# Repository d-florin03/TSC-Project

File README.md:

#  OpenBook – Dispozitiv e-book reader open-source

##  Descriere general

**OpenBook** este un e-book reader ieftin și complet open-source, dezvoltat în cadrul unui start-up care își propune să ofere o alternativă accesibilă și personalizabilă pentru cititul digital. Acest proiect este realizat în echipă, iar scopul este dezvoltarea completă a hardware-ului, de la specificații inițiale până la prototip pregătit pentru producție în masă.
## Diagrama bloc

## 📦 Componente hardware utilizate

    -> Senzor BME688 (senzor multifunctional)
    -> Buton tactil
    -> ESP32-C6-WROOM-1 (modulul principal care contine microcontrolerul ESP32-C6 si o memorie flash SPI de 8 MB)
    -> LED indicator (ADAFRUIT_CHIP-LED0603)
    -> Port USB (USB4110GFA)
    -> Conector JST de 1 mm (JST04_1MM_RA)

## ⚡ Calcul estimativ consum de energie

| Componentă             | Curent estimat | Observații                                   |
|------------------------|----------------|----------------------------------------------|
| ESP32-C6               | ~80-120 mA     | În regim activ cu WiFi                       |
| WS2812B                | ~300 mA        | La luminozitate maximă, toate LED-urile aprinse |
| Senzori proximitate    | ~10-20 mA/senzor| În funcție de tehnologia senzorului          |
| LED-uri statice        | ~10 mA/LED     | În funcție de câte sunt aprinse simultan     |

🔋 **Total estimat**: ~500–600 mA în regim activ continuu. Suficient pentru alimentare USB standard (5V, 1A).

## 📂 Fișiere utile

- `Schematic.png` – Schema electrică completă
- `PCB.png` – Randare PCB + layout
- `README.md` – Acest fișier

---

🛠️ Proiect realizat ca parte a inițiativei **OpenBook**, pentru dezvoltarea unui e-book reader ieftin și open source.

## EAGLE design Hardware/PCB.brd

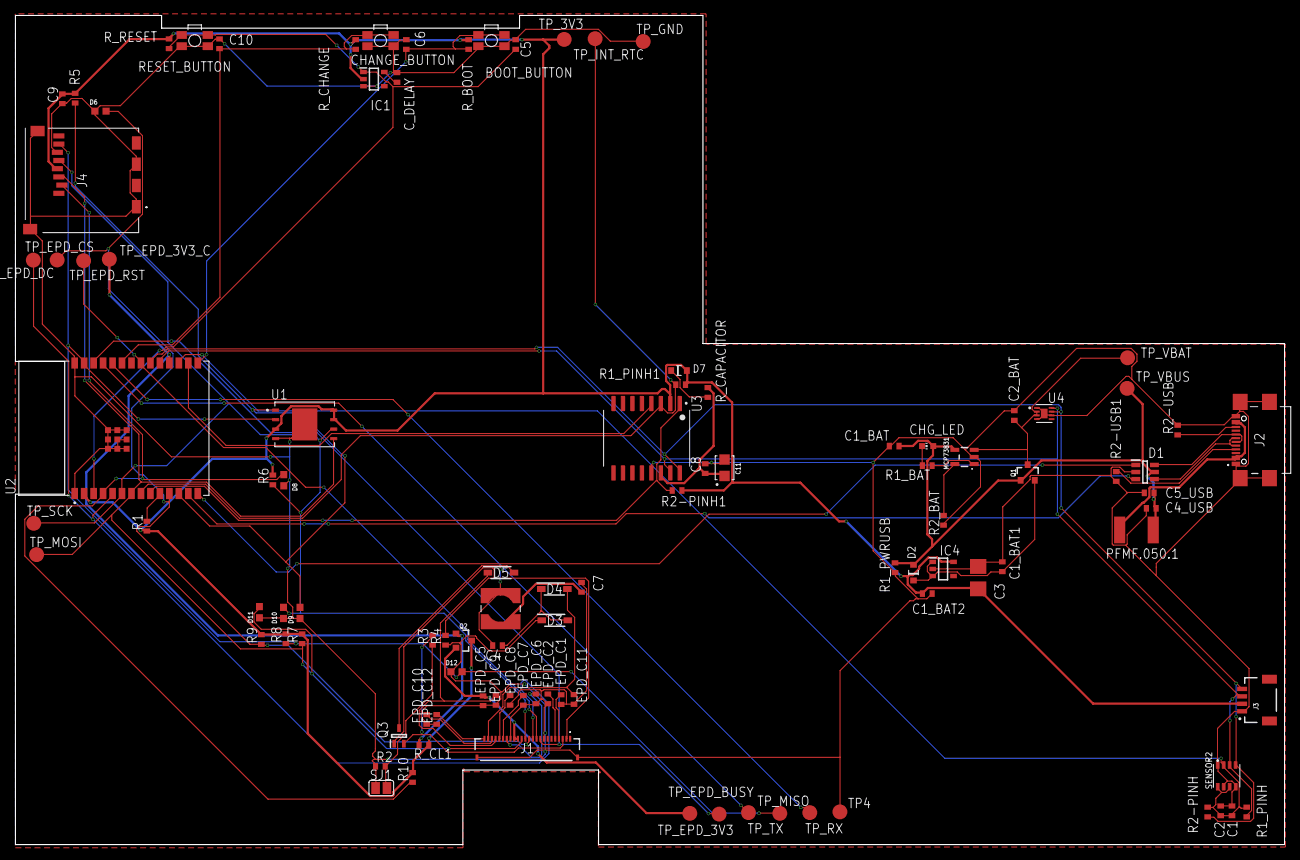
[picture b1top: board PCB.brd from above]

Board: 2 copper layers, 170.2 x 111.2 mm, 103 parts (0 on the bottom side), 56 nets.

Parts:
BOOT_BUTTON: BUTTON_CUSYOMV1; MYBUTTON
C1, C2, C4_USB, C6, C8, C9, C10: 100nF; EAGLE-LTSPICE_C0402
C1_BAT, C2_BAT, C5_USB: 4.7uF; EAGLE-LTSPICE_C0402
C1_BAT1, C1_BAT2: 4.7uF; ESP32_WROVER_EAGLE-LTSPICE_C0402
C3: 100uF TANT; RCL_CT3528
C4: 4.7uF/25V; EAGLE-LTSPICE_C0402
C5: 1uF; EAGLE-LTSPICE_C0402
C7: 10uF; EAGLE-LTSPICE_C0402
C11: CPH3225A; CAPCP3225X100N
CHANGE_BUTTON: BUTTON_CUSYOMV1; MYBUTTON
CHG_LED: ADAFRUIT_CHIP-LED0603
C_DELAY: 100nF; EAGLE-LTSPICE_C0402
D1: USBLC6-2SC6Y; SOT95P280X145-6N
D2, D7: ESP32_WROVER_AVX---SD0805S020S1R0_AVX_SD0805S020S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; ESP32_WROVER_AVX---SD0805S020S1R0_AVX_SD0805S020S1R0_0
D3, D4, D5: MBR0530; SOD3716X135N
D6, D8, D9, D10, D11, D12: PGB1010603MR; DIOC1608X36N
EPD_C1, EPD_C2, EPD_C6, EPD_C7, EPD_C8, EPD_C9, EPD_C10, EPD_C11, EPD_C12: 1uF/50V; EAGLE-LTSPICE_C0402
EPD_C5: 0.1uF/50v; EAGLE-LTSPICE_C0402
IC1: BD5229G-TR; SOT95P280X125-5N
IC4: XC6220A331MR-G; SOT95P280X120-5N
J1: FH34SRJ-24S-0.5SH_99_; FH34SRJ24S05SH99
J2: SAMACSYS_PARTS_USB4110-GF-A; SAMACSYS_PARTS_USB4110GFA
J3: QWIIC_RIGHT_ANGLE; JST04_1MM_RA
J4: 112A-TAAR-R03_ATTEND; 112ATAARR03ATTEND
L1: 68uH; IND_4828-WE-TPC_WRE
MCP73831: ESP32_WROVER_SPARKFUN-IC-POWER_MCP73831; ESP32_WROVER_SPARKFUN-IC-POWER_SOT23-5
PFMF.050.1: ESP32C6_VARISTORCN1812; ESP32C6_VARISTOR_CT/CN1812
Q1, Q2: 20V/4.2A/52mΩ/1.4W; ESP32_WROVER_SPARKFUN-DISCRETESEMI_SOT23-3
Q3: SI1308EDL-T1-GE3; SOT65P210X110-3N
R1: 10k; ESP32_WROVER_EAGLE-LTSPICE_R0402
R1_BAT: 200; ESP32_WROVER_EAGLE-LTSPICE_R0402
R1_PINH, R1_PINH1, R2-PINH, R2-PINH1, R4, R5, R6, R7, R8, R9, R10: 10K; ESP32_WROVER_EAGLE-LTSPICE_R0402
R1_PWRUSB: 100K; ESP32_WROVER_EAGLE-LTSPICE_R0402
R2: 2.2; ESP32_WROVER_EAGLE-LTSPICE_R0402
R2-USB: 5k1; ESP32_WROVER_EAGLE-LTSPICE_R0402
R2-USB1: 5K1; ESP32_WROVER_EAGLE-LTSPICE_R0402
R2_BAT: 2K; ESP32_WROVER_EAGLE-LTSPICE_R0402
R3: 0.47; ESP32_WROVER_EAGLE-LTSPICE_R0402
RESET_BUTTON: BUTTON_CUSYOMV1; MYBUTTON
R_BOOT: 10k; ESP32_WROVER_EAGLE-LTSPICE_R0402
R_CAPACITOR: 15; ESP32_WROVER_EAGLE-LTSPICE_R0402
R_CHANGE: 10k; ESP32_WROVER_EAGLE-LTSPICE_R0402
R_CL1: 10K; ESP32_WROVER_EAGLE-LTSPICE_R0402
R_RESET: 10k; ESP32_WROVER_EAGLE-LTSPICE_R0402
SENSOR2: ESP32_WROVER_BME680_BME680; ESP32_WROVER_BME680_PSON80P300X300X100-8N
SJ1: SJ
TP4: TPTP20R; TP20R
TP_3V3: TPTP20R; TP20R
TP_EPD_3V3, TP_EPD_3V3_C: TPTP20R; TP20R
TP_EPD_BUSY: TPTP20R; TP20R
TP_EPD_CS: TPTP20R; TP20R
TP_EPD_DC: TPTP20R; TP20R
TP_EPD_RST: TPTP20R; TP20R
TP_GND: TPTP20R; TP20R
TP_INT_RTC: TPTP20R; TP20R
TP_MISO: TPTP20R; TP20R
TP_MOSI: TPTP20R; TP20R
TP_RX: TPTP20R; TP20R
TP_SCK: TPTP20R; TP20R
TP_TX: TPTP20R; TP20R
TP_VBAT: TPTP20R; TP20R
TP_VBUS: TPTP20R; TP20R
U1: W25Q512JVEIQ; SON127P600X800X80-9N
U2: ESP32-C6-WROOM-1-N8; XCVR_ESP32-C6-WROOM-1-N8
U3: DS3231SN#; SOIC127P1032X265-16N
U4: MAX17048G+T10; SON50P200X200X80-9N

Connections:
3V3: C1_BAT2.1, C3.+, C9.2, D7.2, IC1.2, IC4.5, J3.2, J4.P4, Q2.3, R1.1, R1_PINH1.2, R2-PINH1.2, R5.2, R6.2, R7.2, R8.2, R9.2, R10.2, R_BOOT.2, R_CHANGE.2, R_CL1.2, R_RESET.2, TP_3V3.TP, U1.3, U1.7, U1.8, U2.2, U3.2
32KHZ: R2-PINH1.1, U2.9, U3.1
DN: D1.4, J2.A7, J2.B7
DP: D1.6, J2.A6, J2.B6
EDP_3V3: C7.1, L1.2
EPD_3V3: EPD_C5.2, J1.15, J1.16, Q2.2, TP_EPD_3V3.TP
EPD_3V3_C: Q2.1, R_CL1.1, TP_EPD_3V3_C.TP, U2.18
EPD_BUSY: J1.9, TP_EPD_BUSY.TP, U2.26
EPD_CS: D6.2, J1.12, R9.1, TP_EPD_CS.TP, U2.11
EPD_DC: J1.11, TP_EPD_DC.TP, U2.5
EPD_RST: J1.10, TP_EPD_RST.TP, U2.21
FLASH_CS: D9.2, R5.1, U1.1, U2.12
GDR: J1.2, Q3.1, R4.2
GND: BOOT_BUTTON.1, BOOT_BUTTON.2, C1.2, C1_BAT.2, C1_BAT1.2, C1_BAT2.2, C2.2, C2_BAT.2, C3.-, C4_USB.2, C5.2, C5_USB.2, C6.2, C7.2, C8.2, C9.1, C10.2, C11.2, CHANGE_BUTTON.1, CHANGE_BUTTON.2, C_DELAY.2, D1.2, D3.1, D6.1, D8.1, D9.1, D10.1, D11.1, D12.1, EPD_C1.1, EPD_C2.1, EPD_C5.1, EPD_C6.1, EPD_C7.1, EPD_C8.1, EPD_C9.1, EPD_C10.1, EPD_C11.1, EPD_C12.1, IC1.3, IC4.2, J1.8, J1.17, J1.MP1, J1.MP2, J2.A1, J2.A12, J2.B1, J2.B12, J2.MP1, J2.MP2, J2.MP3, J2.MP4, J3.1, J4.G1, J4.G2, J4.G3, J4.G4, J4.P6, MCP73831.2, R1_PWRUSB.1, R2.1, R2-USB.2, R2-USB1.1, R2_BAT.1, R4.1, RESET_BUTTON.1, RESET_BUTTON.2, SENSOR2.1, SENSOR2.5, SENSOR2.7, SJ1.1, TP4.TP, TP_GND.TP, U1.4, U1.9, U2.1, U2.28, U2.29_1, U2.29_2, U2.29_3, U2.29_4, U2.29_5, U2.29_6, U2.29_7, U2.29_8, U2.29_9, U3.13, U4.1, U4.4, U4.6, U4.9
GPIO8: R1.2, U2.10
I2C_PW: C1.1, C2.1, R1_PINH.2, R2-PINH.2, SENSOR2.2, SENSOR2.6, SENSOR2.8, U2.17
INT_RTC: R1_PINH1.1, TP_INT_RTC.TP, U2.8, U3.3
IO/BOOT: BOOT_BUTTON.3, BOOT_BUTTON.4, C6.1, R_BOOT.1, U2.15
IO/CHANGE: C10.1, CHANGE_BUTTON.3, CHANGE_BUTTON.4, R_CHANGE.1, U2.23
MISO: D12.2, J4.P7, R8.1, TP_MISO.TP, U1.2, U2.27
MOSI: D11.2, J1.14, J4.P3, R7.1, TP_MOSI.TP, U1.5, U2.7
unnamed: C4.1, D3.2, D4.1
unnamed: EPD_C12.2, J1.24
unnamed: J2.A5, R2-USB1.2
unnamed: J2.B5, R2-USB.1
unnamed: C1_BAT1.1, D2.1, IC4.1, IC4.3, Q1.2
unnamed: D7.1, R_CAPACITOR.1
unnamed: EPD_C10.2, J1.22
unnamed: EPD_C8.2, J1.20
unnamed: EPD_C7.2, J1.19
unnamed: EPD_C6.2, J1.18
unnamed: EPD_C2.2, J1.5
unnamed: C_DELAY.1, IC1.5
unnamed: EPD_C1.2, J1.4
unnamed: MCP73831.5, R2_BAT.2
unnamed: CHG_LED.C, R1_BAT.1
unnamed: MCP73831.1, R1_BAT.2
PREVGH: D5.1, EPD_C9.2, J1.21
PREVGL: D4.2, EPD_C11.2, J1.23
RESE: J1.3, Q3.2, R3.2
RESET: C5.1, IC1.1, RESET_BUTTON.3, RESET_BUTTON.4, R_RESET.1, U2.3
RESE`: R2.2, R3.1, SJ1.2
RTC_RST: U2.16, U3.4
RX: TP_RX.TP, U2.24
SCK: D10.2, J1.13, J4.P5, R6.1, TP_SCK.TP, U1.6, U2.6
SCL: J3.4, R2-PINH.1, SENSOR2.4, U2.20, U3.16, U4.7
SDA: J3.3, R1_PINH.1, SENSOR2.3, U2.19, U3.15, U4.8
SRC: C4.2, D5.2, L1.1, Q3.3
SS_SD: D8.2, J4.P2, R10.1, U2.4
TX: TP_TX.TP, U2.25
USB_D+: D1.1, U2.14
USB_D-: D1.3, U2.13
VBAT: C2_BAT.1, MCP73831.3, Q1.3, TP_VBAT.TP, U4.2, U4.3
VBUS: C1_BAT.1, C4_USB.1, C5_USB.1, CHG_LED.A, D1.5, D2.2, MCP73831.4, PFMF.050.1.2, Q1.1, R1_PWRUSB.2, TP_VBUS.TP
VRTC: C8.1, C11.1, R_CAPACITOR.2, U3.14
VUSB: J2.A4, J2.A9, J2.B4, J2.B9, PFMF.050.1.1

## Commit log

2025-04-06 big commit
2025-04-06 last comm
2025-04-11 Update hardware
2025-04-11 last update

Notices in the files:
parts and their libraries:
COPYRIGHT: Copyright (C) 2024 Ultra Librarian. All rights reserved.
